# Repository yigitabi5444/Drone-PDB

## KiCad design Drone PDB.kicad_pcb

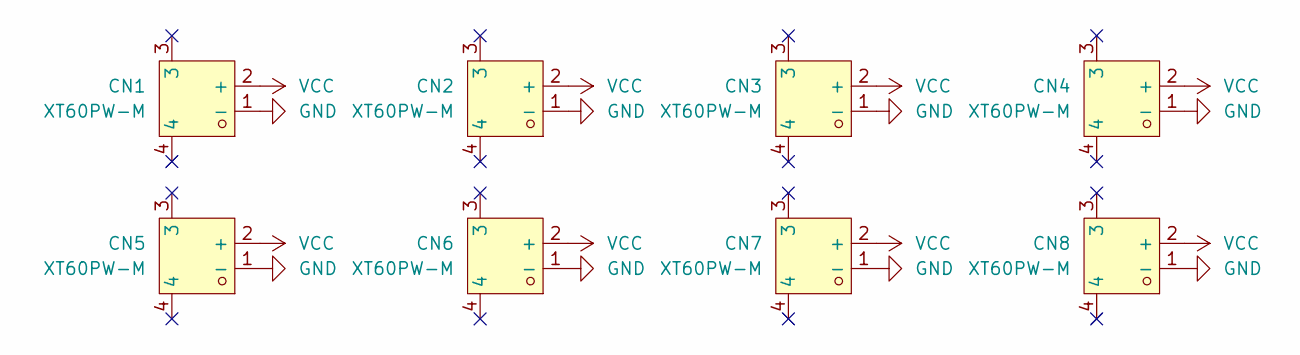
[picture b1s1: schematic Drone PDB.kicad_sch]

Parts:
CN1, CN2, CN3, CN4, CN5, CN6, CN7, CN8: XT60PW-M; CONN-TH_XT60PW-M; LCSC Part C98732

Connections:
GND: CN1.1 (-), CN2.1 (-), CN3.1 (-), CN4.1 (-), CN5.1 (-), CN6.1 (-), CN7.1 (-), CN8.1 (-)
VCC: CN1.2 (+), CN2.2 (+), CN3.2 (+), CN4.2 (+), CN5.2 (+), CN6.2 (+), CN7.2 (+), CN8.2 (+)

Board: 2 copper layers, 8 parts (0 on the bottom side), 2 nets, no tracks yet.

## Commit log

2023-02-05 SCH done
2023-02-05 drone pcb done
